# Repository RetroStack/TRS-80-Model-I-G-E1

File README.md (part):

# TRS-80 Model 1 (Rev G) Replica - E1

This project is a faithful reimplementation of the mainboard of the iconic TRS-80 Model 1 (Revision G) computer. My own revision, the E1, is designed to replicate the original system's functionality by using a PCB design 1-to-1 to the original, including components, interfaces, and even traces. The entire project is available under the MIT license.

## Project Details

### Latest Files

In the "Latest" folder, you'll find the most up-to-date design files, including:

- Gerber files suitable for popular online PCB manufacturers like [PCBWay](/Latest/TRS80_Model_I_G_E1_Gerber_PCBWay.zip) and [JLCPCB](/Latest/TRS80_Model_I_G_E1_Gerber_JLCPCB.zip). Most manufacturers should be fine with either.
- A Bill of Materials (BOM) in both [CSV](/Latest/TRS80_Model_I_G_E1_BOM.csv) and [PDF](/Latest/TRS80_Model_I_G_E1_BOM.pdf) formats. (Also, see the list below.)
- Layers exported in PDF and SVG formats.
- The [full schematics](/Latest/TRS80_Model_I_G_E1_Schematics.pdf) of the E1 replica which is 1:1 to the original G board.
- A simple [Assembly Guide](/Latest/TRS80_Model_I_G_E1_AssemblyGuide.pdf) in PDF format.

### Implementation

E1 has been implemented using KiCAD 7. The KiCAD project files are included in this repository.

### Assembly Instructions

For each step, check if there is a connection between pad 1, 8, 9, 16 on Z18 (all four corners of the dynamic RAM IC). That IC needs all 3 voltages with ground. If any of them are shorted, then you know what you did most recently. Finding the cause of the short should then be relatively easy.

1. (optional) Install sockets for all ICs. You probably want to skip Z3 and Z71, if you want to use DIP switches instead.
2. Install all diodes. These diodes are hard to read and if you accidentally mix them up, you might end up with incorrect voltages on the rails. Also, make sure to orient them correctly. There should be a black band on one side of the glass diode. Match this with the "thicker" side of the diode on the PCB. Installing first the shorter components will make sure you still can flip the board around and solder things easily.
3. Install all resistors. Resistors do not have an orientation. Skip the potentiometers for now. When installing the C*R67 (yes, there is a "C*"), this is an unmarked resistor between relay and the R21 potentiometer. This should be a 220 ohm 0.5W resistor (a bit larger than the others). There is another R67 which is next to Z42, which is a 4.7k Ohm resistor 0.25W (same size as most of the others).
4. Install all disc-like capacitors. Do not install the electrolytic capacitors yet! All other capacitors are rather small and orientation isn't important. The C58 next to the relay stays empty. Do not install it there. Instead, there is another (!!!) C58 next to the ROMs in the middle of the PCB.
5. Install all transistors, including the ones with the heatsinks. The TIP29 should go into Q3 (metal side away from board towards the Q3 label) while the TIP32C should go into Q6 (lay flat with heatsink; bend legs wit needle-nose pliers to fit). Don't forget to add thermal paste between heatsink and transistors. Make sure to add the screws and nuts and that it fits tightly as the screws themself connect traces. Not having them properly installed will result in a non-functioning system. The smaller black transistors have one flat side. These should all face towards the bottom of the board towards all the ICs (the middle leg needs to be bend slightly out to fit).
6. Install the crystal (no orientation), relay (match orientation on PCB; three legs towards the bottom), full-bridge rectifier (CR8; match "+" marking on component with PCB marking), all DIN connectors, both switches, keyboard connector (if bend, bend it upwards - towards the CPU to fit in the case), and potentiometers (only goes in one way). You can also install the DIP switches, if you go with that (numbers on the left side and "ON" label on the right).
7. Install all electrolytic capacitors. Make sure the orientation is correct! Modern capacitors mark the "-" side. On the PCB, the positive side is marked. All electrolytic capacitors on the PCB are oriented the same way EXCEPT C42 (!!!). Incorrect orientation may result in a small explosion (loud and smokey, but probably not dangerous).
8. Only install Z1 & Z2 to calibrate the power supply. Don't install any of the other ICs yet!!!
9. Get Multimeter ready in voltage mode. Connect power, turn on S1. If something starts to smell burned, turn S1 off and disconnect power.
10. Check voltage between pad 1 (-5V) and pad 16 (GND) on Z18. It should be around -5.1V to -5.2V. Since this is clamped with a zener diode, this should be pretty accurate. There is nothing that needs to be calibrated here. If the voltage goes beyond -5.3V, check R19 (may be really hot! careful!). If R19 is hot to the touch, your power supply is probably broken. (I've seen this on one power supply while another one didn't have that problem.)
11. Check voltage between pad 8 (+12V) and pad 16 (GND) on Z18. It should be around +12.0V. If it isn't, change the R10 potentiometer. If it is +/-0.5V off, then this is fine. But, try to get it as close to the desired voltage as possible.
12. (You need to calibrate +12V first before going to this next step!!!) Check voltage between pad 9 (+5V) and pad 16 (GND) on Z18. It should be around +5.0V. If it isn't, change the R5 potentiometer. If it is +/-0.5V off, then this is fine. But, also here, try to get it close to the desired voltage.
13. Re-check all the voltages after calibration, just to be sure.
14. Turn off S1 and disconnect power. Do this for each of the following steps. After each change, re-check the voltages at Z18 to find shorts quickly.
15. Start inserting the ICs. Focus on the 74LSxx ICs first. They are cheap and are easily recoverable in case there is a short somewhere and you start frying ICs. May be do 2-4 chips at a time and re-check the voltages at Z18. Do this systematically from left to right and top to bottom, so you know which you inserted most recently. If one of the voltages changes significantly at Z18 (+/- 2V and more), then you probably have a short with the most recent ICs. Do not insert the CPU, ROMs, character generator, and RAMs (static (2102) and dynamic ones (4116)) for now. They are expensive to replace if they fry.
16. Insert the 74Cxx ICs. These ICs are also cheap, but they are very sensitive. If all voltages are good, then they are good to install.
17. Connect to a monitor. Use a CRT, if possible, as video calibration is easier. LCD works too, but the reaction time is slow and requires a longer wait time after each change.
18. After turning on monitor and S1, you should see white blocks on a black background. If you don't see it, try changing R20 (vertical sync) and R21 (horizontal sync). If all fails, try to center both potentiometer. This usually results in a non-optimal picture, but a picture non-the-less. You can then calibrate.
19. (Don't forget to turn off system!) Insert the static video RAM (2102). These ICs only require +5V.
20. Now you need to configure the memory addresses and the memory configuration. With DIP switches, configure as follows:

- (memory location configuration) Z3: Switch 1 to the left, while all others are to the right. This is the configuration for 12k ROM and 16k RAM.
- (memory type configuration) Z71: Switch 1, 3, 5 to the right while all others are to the left. This is the configuration for 16k RAM modules.

21. Insert the dynamic RAM (4116). These ICs require all three voltages.
22. Insert CPU. Not much should have changed from the video calibration up until now. The next step will change that.
23. Insert character generator. Instead of white blocks, you should see (random) characters. The system doesn't clear the video memory yet since no ROM is installed.
24. Install ROM. This should be a Level II v1.3. If you don't have this, you probably need additional circuity to make these work. You can also burn the [diag ROM](https://github.com/misterblack1/trs80-diagnosticrom/blob/main/trs80m13diag.bin) on a 2k ROM to test the system. The diag ROM should work for all revisions of the TRS-80 Model 1.
25. At this point, you should see a prompt showing "Memory Size?" that keeps blinking (if it is the normal system ROM). The reason for the blinking is that the keyboard is not yet connected and the system recognizes keypresses. Install the keyboard with the IDC cable (if you installed a header).
26. Now, you should be able to use the system. Try to hold the left SHIFT key and press the right arrow key and the text size should increase, switching the video modes. (It is OK when some characters are skipped. That is normal.) The CLEAR key should reset it to the original video mode and clear the screen.
27. Try running a "Hello World!" program: 10 PRINT "Hello World!" (Return) 20 GOTO 10 (Return) RUN (Return). You can stop with the BREAK key.

### Ordering Instructions

When ordering the board from a PCB manufacturer, you can select the following to get a more faithful version of the board:

```
Dimension: 407mm x 184mm
Layers: 2
Base Material: FR-4 TG 135-140 (and up)
PCB Thickness: 1.6mm
PCB Color: Green
Silkscreen Color: White
Via Covering: Untented
Surface Finish: Lead Free HASL
Outer Copper Weight: 1oz
Gold Fingers / Card Edge: yes (chamfer: 30 degrees)
Castellated Holes: no
```

Additionally, supply the following comment for the manufacturer:

> Card edge is only on the upper right. The bottom right is just a connector and does not need to be chamfered.
>
> There are some missing pads on the top layer. That is correct. Please leave them as-is.

This addresses recurring questions from some of the interesting designs that were used on the original board which was replicated. See the ["Curiosities"](/Curiosities.md) page.

### Bill of Materials (BOM)

Below is a list of materials needed to assemble a complete system. Please note that the links and prices (scroll to the right to see them; as of January 22, 2024) will not be updated in the future and should only be used as a reference for locating the correct items.

Note: Links and alternatives are provided to assist you in finding the necessary components. I cannot guarantee the complete accuracy or reliability of all these links and alternatives. Please check it for yourself!

| Reference                                                                                                                                                                | Qty | Description                                                          | Source Comment                                               | Source Cost USD | Source Total Cost USD | Source                                                                                                                                 |
| ------------------------------------------------------------------------------------------------------------------------------------------------------------------------ | --- | -------------------------------------------------------------------- | ------------------------------------------------------------ | --------------- | --------------------- | -------------------------------------------------------------------------------------------------------------------------------------- |
| C1                                                                                                                                                                       | 1   | 220uF 16V polarized capacitor                                        |                                                              | 1.48            | 1.48                  | [Mouser](https://www.mouser.com/ProductDetail/598-227TTA050M)                                                                          |
| C2, C4, C5, C10, C11, C57                                                                                                                                                | 6   | 10uF 16V polarized capacitor                                         |                                                              | 0.29            | 1.74                  | [Mouser](https://www.mouser.com/ProductDetail/598-106RMR050M)                                                                          |
| C3, C7, C14, C15                                                                                                                                                         | 4   | 0.01uF 24V (103) capacitor                                           |                                                              | 0.23            | 0.92                  | [Mouser](https://www.mouser.com/ProductDetail/594-D103Z25Z5VF63L6R)                                                                    |
| C6                                                                                                                                                                       | 1   | 100uF 16V polarized capacitor                                        |                                                              | 0.37            | 0.37                  | [Mouser](https://www.mouser.com/ProductDetail/647-UVZ1J101MPD)                                                                         |
| C8                                                                                                                                                                       | 1   | 2200uF 35V polarized capacitor                                       |                                                              | 5.31            | 5.31                  | [Mouser](https://www.mouser.com/ProductDetail/598-228TTA063M)                                                                          |
| C9                                                                                                                                                                       | 1   | 10000uF 16V polarized capacitor                                      |                                                              | 7.87            | 7.87                  | [Mouser](https://www.mouser.com/ProductDetail/598-109TTA025M)                                                                          |
| C12, C13                                                                                                                                                                 | 2   | 470pF (471) capacitor                                                |                                                              | 0.23            | 0.46                  | [Mouser](https://www.mouser.com/ProductDetail/594-D471K20Y5PH6UJ5R)                                                                    |
| C16, C17, C18, C19, C22, C23, C28, C29, C30, C31, C32, C33, C34, C35, C36, C37, C38, C39, C40, C41, C44, C45, C46, C47, C48, C49, C50, C51, C52, C53, C54, C55, C56, C58 | 34  | 0.1uF 25V (104) capacitor                                            |                                                              | 0.17            | 5.78                  | [Mouser](https://www.mouser.com/ProductDetail/594-K104K10X7RF53L2)                                                                     |
| C20                                                                                                                                                                      | 1   | 330pF (331) capacitor                                                |                                                              | 0.3             | 0.3                   | [Mouser](https://www.mouser.com/ProductDetail/594-F331K29Y5RP6UK5R)                                                                    |
| C21                                                                                                                                                                      | 1   | 750pF (750) capacitor                                                |                                                              | 0.37            | 0.37                  | [Mouser](https://www.mouser.com/ProductDetail/80-C322C751K3G5TA)                                                                       |
| C24, C25                                                                                                                                                                 | 2   | 220pF (221) capacitor                                                |                                                              | 0.23            | 0.46                  | [Mouser](https://www.mouser.com/ProductDetail/594-D221K20Y5PF63J5R)                                                                    |
| C26                                                                                                                                                                      | 1   | 0.047uF (47nF) capacitor                                             |                                                              | 1.9             | 1.9                   | [Mouser](https://www.mouser.com/ProductDetail/594-222236755473)                                                                        |
| C27                                                                                                                                                                      | 1   | 0.022uF (22nF) capacitor                                             |                                                              | 1.34            | 1.34                  | [Mouser](https://www.mouser.com/ProductDetail/594-2222-366-45223)                                                                      |
| C42                                                                                                                                                                      | 1   | 22uF 16V polarized capacitor                                         |                                                              | 0.1             | 0.1                   | [Mouser](https://www.mouser.com/ProductDetail/710-860010372002)                                                                        |
| C43                                                                                                                                                                      | 1   | 47pF (47) capacitor                                                  |                                                              | 0.4             | 0.4                   | [Mouser](https://www.mouser.com/ProductDetail/594-S470K25SL0N63L6R)                                                                    |
| CR1                                                                                                                                                                      | 1   | 1N4735 Zener diode                                                   |                                                              | 0.25            | 0.25                  | [Mouser](https://www.mouser.com/ProductDetail/512-1N4735A)                                                                             |
| CR2                                                                                                                                                                      | 1   | 1N5231 Zener diode                                                   |                                                              | 0.15            | 0.15                  | [Mouser](https://www.mouser.com/ProductDetail/512-1N5231B)                                                                             |
| CR3, CR4, CR5, CR6, CR7                                                                                                                                                  | 5   | 1N4148                                                               | Diode                                                        | 0.1             | 0.5                   | [Mouser](https://www.mouser.com/ProductDetail/512-1N4148)                                                                              |
| CR8                                                                                                                                                                      | 1   | MDA202 Diode bridge, +ve/AC/AC/-ve                                   | Replacement                                                  | 0.61            | 0.61                  | [Mouser](https://www.mouser.com/ProductDetail/621-KBP210G)                                                                             |
| CR9, CR10                                                                                                                                                                | 2   | 1N982 Schottky diode                                                 | Replacement, Lower (39V instead of 75V)                      | 0.26            | 0.52                  | [Mouser](https://www.mouser.com/ProductDetail/78-1N4754A-TAP)                                                                          |
| J1, J2, J3                                                                                                                                                               | 3   | 5-pin DIN connector (5-pin DIN-5 stereo)                             | For metal connector only. The plastic plugs don't fit in it. | 0.386           | 1.158                 | [AliExpress](https://www.aliexpress.us/item/2255801077942335.html)                                                                     |
| J100                                                                                                                                                                     | 1   | 01x20 Generic connector, single row, 01x20                           |                                                              | 0.5             | 0.5                   | [Mouser](https://www.mouser.com/ProductDetail/649-1012937992002BLF)                                                                    |
| K1                                                                                                                                                                       | 1   | Relay SPST, Normally Open                                            | Slightly smaller than original                               | 14.84           | 14.84                 | [DigiKey](https://www.digikey.com/en/products/detail/sensata-cynergy3/S2-05P/4425813)                                                  |
| Q1                                                                                                                                                                       | 1   | 2N3904 0.2A Ic, 40V Vce, Small Signal NPN Transistor, TO-92          |                                                              | 0.35            | 0.35                  | [Mouser](https://www.mouser.com/ProductDetail/512-2N3904BU)                                                                            |
| Q2, Q5                                                                                                                                                                   | 2   | 2N3906 -0.2A Ic, -40V Vce, Small Signal PNP Transistor, TO-92        |                                                              | 0.28            | 0.56                  | [Mouser](https://www.mouser.com/ProductDetail/512-2N3906BU)                                                                            |
| Q3                                                                                                                                                                       | 1   | TIP29A (BCE) NPN transistor                                          |                                                              | 1.01            | 1.01                  | [Mouser](https://www.mouser.com/ProductDetail/863-TIP29AG)                                                                             |
| Q4                                                                                                                                                                       | 1   | 2N6594 (BEC) PNP transistor                                          | Replacement (Other: RS2040, MJ2955G)                         | 4.73            | 4.73                  | [Mouser](https://www.mouser.com/ProductDetail/863-MJ2955G)                                                                             |
| Q6                                                                                                                                                                       | 1   | MJE34 (BCE) PNP transistor                                           | Replacement                                                  | 0.67            | 0.67                  | [Mouser](https://www.mouser.com/ProductDetail/511-TIP32C)                                                                              |
| -                                                                                                                                                                        | 1   | Q4 Heatsink                                                          |                                                              | 1.01            | 1.01                  | [Mouser](https://www.mouser.com/ProductDetail/532-506007B00)                                                                           |
| -                                                                                                                                                                        | 1   | Q6 Heatsink                                                          | Smaller than original                                        | 0.3             | 0.3                   | [Mouser](https://www.mouser.com/ProductDetail/532-507302B00)                                                                           |
| R1                                                                                                                                                                       | 1   | 68 Resistor 0.25W                                                    |                                                              | 0.1             | 0.1                   | [Mouser](https://www.mouser.com/ProductDetail/603-CFR-25JB-52-68R)                                                                     |
| R2                                                                                                                                                                       | 1   | 2.7k Resistor 0.25W                                                  |                                                              | 0.1             | 0.1                   | [Mouser](https://www.mouser.com/ProductDetail/603-CFR-25JR-522K7)                                                                      |
| R3                                                                                                                                                                       | 1   | 750 Resistor 0.25W                                                   |                                                              | 0.1             | 0.1                   | [Mouser](https://www.mouser.com/ProductDetail/603-CFR-25JB-52-750R)                                                                    |
| R4                                                                                                                                                                       | 1   | 0.33 Resistor 2W                                                     |                                                              | 0.45            | 0.45                  | [Mouser](https://www.mouser.com/ProductDetail/603-CFR2WSJT-73-0R33)                                                                    |
| R5, R10                                                                                                                                                                  | 2   | 1k Potentiometer                                                     |                                                              | 0.57            | 1.14                  | [Mouser](https://www.mouser.com/ProductDetail/531-PT10H-1K-S)                                                                          |
| R6, R7, R16, R53                                                                                                                                                         | 4   | 1.2k Resistor 0.25W                                                  |                                                              | 0.1             | 0.4                   | [Mouser](https://www.mouser.com/ProductDetail/603-CFR-25JB-52-1K2)                                                                     |
| R8                                                                                                                                                                       | 1   | 100k Resistor 0.25W                                                  |                                                              | 0.1             | 0.1                   | [Mouser](https://www.mouser.com/ProductDetail/603-CFR-25JB-52-100K)                                                                    |
| R9, R11, R12                                                                                                                                                             | 3   | 3.3k Resistor 0.25W                                                  |                                                              | 0.1             | 0.3                   | [Mouser](https://www.mouser.com/ProductDetail/603-CFR-25JB-52-3K3)                                                                     |
| R13                                                                                                                                                                      | 1   | 2.2k Resistor 0.25W                                                  |                                                              | 0.1             | 0.1                   | [Mouser](https://www.mouser.com/ProductDetail/603-CFR-25JT-52-2K2)                                                                     |
| R14                                                                                                                                                                      | 1   | 12k Resistor 0.25W                                                   |                                                              | 0.1             | 0.1                   | [Mouser](https://www.mouser.com/ProductDetail/603-CFR-25JB-52-12K)                                                                     |
| R15                                                                                                                                                                      | 1   | 1.5k Resistor 0.25W                                                  |                                                              | 0.1             | 0.1                   | [Mouser](https://www.mouser.com/ProductDetail/603-CFR-25JT-52-1K5)                                                                     |
| R17                                                                                                                                                                      | 1   | 2k Resistor 0.25W                                                    |                                                              | 0.1             | 0.1                   | [Mouser](https://www.mouser.com/ProductDetail/603-CFR-25JB-52-2K)                                                                      |
| R18                                                                                                                                                                      | 1   | 5.6 Resistor 3W                                                      |                                                              | 0.57            | 0.57                  | [Mouser](https://www.mouser.com/ProductDetail/279-EP3WSS5R6J)                                                                          |
| R19, C_R67                                                                                                                                                               | 2   | 220 Resistor 0.5W                                                    |                                                              | 0.1             | 0.1                   | [Mouser](https://www.mouser.com/ProductDetail/603-CFR-50JB-52-220R)                                                                    |
| R20, R21                                                                                                                                                                 | 2   | 100k Potentiometer                                                   |                                                              | 0.57            | 1.14                  | [Mouser](https://www.mouser.com/ProductDetail/531-PT10H-100K-S)                                                                        |
| R22                                                                                                                                                                      | 1   | 75 Resistor 0.25W                                                    |                                                              | 0.1             | 0.1                   | [Mouser](https://www.mouser.com/ProductDetail/603-CFR-25JB-52-75R)                                                                     |
| R23                                                                                                                                                                      | 1   | 120 Resistor 0.25W                                                   |                                                              | 0.1             | 0.1                   | [Mouser](https://www.mouser.com/ProductDetail/603-CFR-25JB-52-120R)                                                                    |
| R24                                                                                                                                                                      | 1   | 680k Resistor 0.25W                                                  |                                                              | 0.1             | 0.1                   | [Mouser](https://www.mouser.com/ProductDetail/603-CFR-25JB-52-680K)                                                                    |
| R25                                                                                                                                                                      | 1   | 1.6M Resistor 0.25W                                                  |                                                              | 0.1             | 0.1                   | [Mouser](https://www.mouser.com/ProductDetail/603-CFR-25JB-52-1M6)                                                                     |
| R26, R42                                                                                                                                                                 | 2   | 1M Resistor 0.25W                                                    |                                                              | 0.1             | 0.2                   | [Mouser](https://www.mouser.com/ProductDetail/603-CFR-25JT-52-1M)                                                                      |
| R27, R64                                                                                                                                                                 | 2   | 330 Resistor 0.25W                                                   |                                                              | 0.1             | 0.2                   | [Mouser](https://www.mouser.com/ProductDetail/603-CFR-25JB-52-330R)                                                                    |
| R28                                                                                                                                                                      | 1   | 270 Resistor 0.25W                                                   |                                                              | 0.1             | 0.1                   | [Mouser](https://www.mouser.com/ProductDetail/603-CFR-25JB-52-270R)                                                                    |
| R29                                                                                                                                                                      | 1   | 1.8k Resistor 0.25W                                                  |                                                              | 0.1             | 0.1                   | [Mouser](https://www.mouser.com/ProductDetail/603-CFR-25JB-52-1K8)                                                                     |
| R30                                                                                                                                                                      | 1   | 47 Resistor 0.25W                                                    |                                                              | 0.1             | 0.1                   | [Mouser](https://www.mouser.com/ProductDetail/603-CFR-25JB-52-47R)                                                                     |
| R31                                                                                                                                                                      | 1   | 10 Resistor 0.25W                                                    |                                                              | 0.1             | 0.1                   | [Mouser](https://www.mouser.com/ProductDetail/603-CFR-25JT-52-10R)                                                                     |
| R32, R43, R44, R47, R65                                                                                                                                                  | 5   | 10k Resistor 0.25W                                                   |                                                              | 0.1             | 0.5                   | [Mouser](https://www.mouser.com/ProductDetail/603-CFR-25JB-52-10K)                                                                     |
| R33, R36                                                                                                                                                                 | 2   | 360k Resistor 0.25W                                                  |                                                              | 0.1             | 0.2                   | [Mouser](https://www.mouser.com/ProductDetail/603-CFR-25JB-52-360K)                                                                    |
| R34, R35, R38, R41, R45                                                                                                                                                  | 5   | 470k Resistor 0.25W                                                  |                                                              | 0.1             | 0.5                   | [Mouser](https://www.mouser.com/ProductDetail/603-CFR-25JB-52-470K)                                                                    |
| R37                                                                                                                                                                      | 1   | 560k Resistor 0.25W                                                  |                                                              | 0.1             | 0.1                   | [Mouser](https://www.mouser.com/ProductDetail/603-CFR-25JB-52-560K)                                                                    |
| R39, R40, R48, R49, R50, R51, R57, R58, R59, R60, R61, R62, R63, R66, R67, R68, R69                                                                                      | 17  | 4.7k Resistor 0.25W                                                  |                                                              | 0.1             | 1.7                   | [Mouser](https://www.mouser.com/ProductDetail/603-CFR-25JB-52-4K7)                                                                     |
| R46, R52                                                                                                                                                                 | 2   | 910 Resistor 0.25W                                                   |                                                              | 0.1             | 0.2                   | [Mouser](https://www.mouser.com/ProductDetail/603-CFR-25JB-52-910R)                                                                    |
| R54, R55                                                                                                                                                                 | 2   | 7.5k Resistor 0.25W                                                  |                                                              | 0.1             | 0.2                   | [Mouser](https://www.mouser.com/ProductDetail/603-CFR-25JB-52-7K5)                                                                     |
| R56                                                                                                                                                                      | 1   | 220k Resistor 0.25W                                                  |                                                              | 0.1             | 0.1                   | [Mouser](https://www.mouser.com/ProductDetail/603-CFR-25JB-52-220K)                                                                    |
| S1                                                                                                                                                                       | 1   | Power 4PST                                                           | No Cap                                                       | 4.34            | 4.34                  | [DigiKey](https://www.digikey.com/en/products/detail/c-k/F4UEE/417520)                                                                 |
| S2                                                                                                                                                                       | 1   | Reset DPST                                                           | Red Cap                                                      | 1.815           | 1.815                 | [AliExpress](https://www.aliexpress.us/item/3256804467086494.html)                                                                     |
| Y1                                                                                                                                                                       | 1   | 10.6445 MHz Two pin crystal                                          | Only 10.6MHz                                                 | 0.73            | 0.73                  | [Mouser](https://www.mouser.com/ProductDetail/449-LFXTAL028537BULK)                                                                    |
| Z1, Z2                                                                                                                                                                   | 2   | LM723C Linear Regulator (adjustable)                                 |                                                              | 1.04            | 2.08                  | [Mouser](https://www.mouser.com/ProductDetail/595-UA723CN)                                                                             |
| Z3, Z71                                                                                                                                                                  | 2   | 8-Bit DIP Switch                                                     | Replacement                                                  | 2.07            | 4.14                  | [Mouser](https://www.mouser.com/ProductDetail/710-418117270908)                                                                        |
| Z4                                                                                                                                                                       | 1   | LM3900 Quad operational amplifier                                    |                                                              | 0.6             | 0.6                   | [Mouser](https://www.mouser.com/ProductDetail/595-LM3900NE4)                                                                           |
| Z5                                                                                                                                                                       | 1   | 74C00 quad 2-input NAND gate                                         | 74HC00 works in a pinch, but suboptimal video.               | ~2.50           | ~2.50                 | eBay/Jameco                                                                                                                            |
| Z6, Z57                                                                                                                                                                  | 2   | 74C04 Hex Inverter                                                   | 74HC00 works in a pinch, but suboptimal video.               | 2.49            | 4.98                  | [Jameco](https://www.jameco.com/webapp/wcs/stores/servlet/ProductDisplay?storeId=10001&langId=-1&catalogId=10001&productId=44231)      |
| Z7, Z69, Z70                                                                                                                                                             | 3   | 74LS74 Dual D Flip-flop, Set & Reset                                 |                                                              | 0.49            | 1.47                  | [Mouser](https://www.mouser.com/ProductDetail/595-SN74LS74AN)                                                                          |
| Z8                                                                                                                                                                       | 1   | 74LS153 Dual Multiplexer 4 to 1                                      |                                                              | 1.13            | 1.13                  | [Mouser](https://www.mouser.com/ProductDetail/595-SN74LS153N)                                                                          |
| Z9, Z42, Z52                                                                                                                                                             | 3   | 74LS04 Hex Inverter                                                  |                                                              | 0.67            | 2.01                  | [Mouser](https://www.mouser.com/ProductDetail/595-SN74LS04N)                                                                           |
| Z10, Z11                                                                                                                                                                 | 2   | 74LS166 Shift Register 8-bit, parallel load                          |                                                              | 1.24            | 2.48                  | [Mouser](https://www.mouser.com/ProductDetail/595-SN74LS166AN)                                                                         |
| Z12, Z32, Z50, Z65                                                                                                                                                       | 4   | 74LS93 Divide by 2 & 8 counter                                       |                                                              | 3.04            | 12.16                 | [Mouser](https://www.mouser.com/ProductDetail/595-SN74LS93N)                                                                           |
| Z13, Z14, Z15, Z16, Z17, Z18, Z19, Z20                                                                                                                                   | 8   | 4116 16kBit x 1 Bit Dynamic RAM                                      |                                                              | 3.95            | 31.6                  | [Jameco](https://www.jameco.com/z/4116-15-Major-Brands-IC-4116-15-DRAM-16-384-Bit-16Kx1-150ns-5V_41339.html)                           |
| Z21                                                                                                                                                                      | 1   | 74LS156 Dual 2 to 4 lines Decoder/Demultiplexer, Open Collector      |                                                              | 0.75            | 0.75                  | [Mouser](https://www.mouser.com/ProductDetail/595-SN74LS156N)                                                                          |
| Z22, Z38, Z39, Z44, Z55, Z60, Z67, Z68, Z72, Z75, Z76                                                                                                                    | 11  | 74LS367 Hex buffer 3-State outputs                                   |                                                              | 1.44            | 15.84                 | [Mouser](https://www.mouser.com/ProductDetail/595-SN74LS367AN)                                                                         |
| Z23, Z25, Z36, Z73                                                                                                                                                       | 4   | 74LS32 Quad 2-input OR                                               |                                                              | 0.56            | 2.24                  | [Mouser](https://www.mouser.com/ProductDetail/595-SN74LS32N)                                                                           |
| Z24, Z53                                                                                                                                                                 | 2   | 74LS132 Quad 2-input NAND Schmitt trigger                            |                                                              | 1.03            | 2.06                  | [Mouser](https://www.mouser.com/ProductDetail/595-SN74LS132N)                                                                          |
| Z26                                                                                                                                                                      | 1   | 74LS20 Dual 4-input NAND                                             |                                                              | 1.28            | 1.28                  | [Mouser](https://www.mouser.com/ProductDetail/595-SN74LS20N)                                                                           |
| Z27, Z59                                                                                                                                                                 | 2   | 74LS175 4-bit D Flip-Flop, reset                                     |                                                              | 1.02            | 2.04                  | [Mouser](https://www.mouser.com/ProductDetail/595-SN74LS175N)                                                                          |
| Z28                                                                                                                                                                      | 1   | 74LS174 Hex D-type Flip-Flop, reset                                  |                                                              | 1.12            | 1.12                  | [Mouser](https://www.mouser.com/ProductDetail/595-SN74LS174N)                                                                          |
| Z29                                                                                                                                                                      | 1   | MCM6670 128 x 7 x 5 Character Generator                              | Adapter needed                                               |                 | 0                     | [GitHub](https://github.com/RetroStack/MCM776x_CharGen_Adapter)                                                                        |
| Z30, Z37                                                                                                                                                                 | 2   | 74LS02 quad 2-input NOR gate                                         |                                                              | 0.55            | 1.1                   | [Mouser](https://www.mouser.com/ProductDetail/595-SN74LS02N)                                                                           |
| Z31, Z35, Z43, Z49, Z51, Z64                                                                                                                                             | 6   | 74LS157 Quad 2 to 1 line Multiplexer                                 |                                                              | 0.88            | 5.28                  | [Mouser](https://www.mouser.com/ProductDetail/595-SN74LS157N)                                                                          |
| Z33                                                                                                                                                                      | 1   | 2364 (20-pin Low) 2364 64kBit (8kb x 8) PROM                         | Adapter needed                                               |                 | 0                     | -                                                                                                                                      |
| Z34                                                                                                                                                                      | 1   | 2332 (20- & 21-pin Low) 2332 32kBit (4kb x 8) PROM                   | Adapter needed                                               |                 | 0                     | -                                                                                                                                      |
| Z40                                                                                                                                                                      | 1   | Z80 CPU                                                              |                                                              | 9.62            | 9.62                  | [Mouser](https://www.mouser.com/ProductDetail/692-Z84C0010PEG)                                                                         |
| Z41                                                                                                                                                                      | 1   | 75452 Dual-Peripheral Drivers for High-Current, High-Speed Switching |                                                              | 0.9             | 0.9                   | [Mouser](https://www.mouser.com/ProductDetail/595-SN75452BP)                                                                           |
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
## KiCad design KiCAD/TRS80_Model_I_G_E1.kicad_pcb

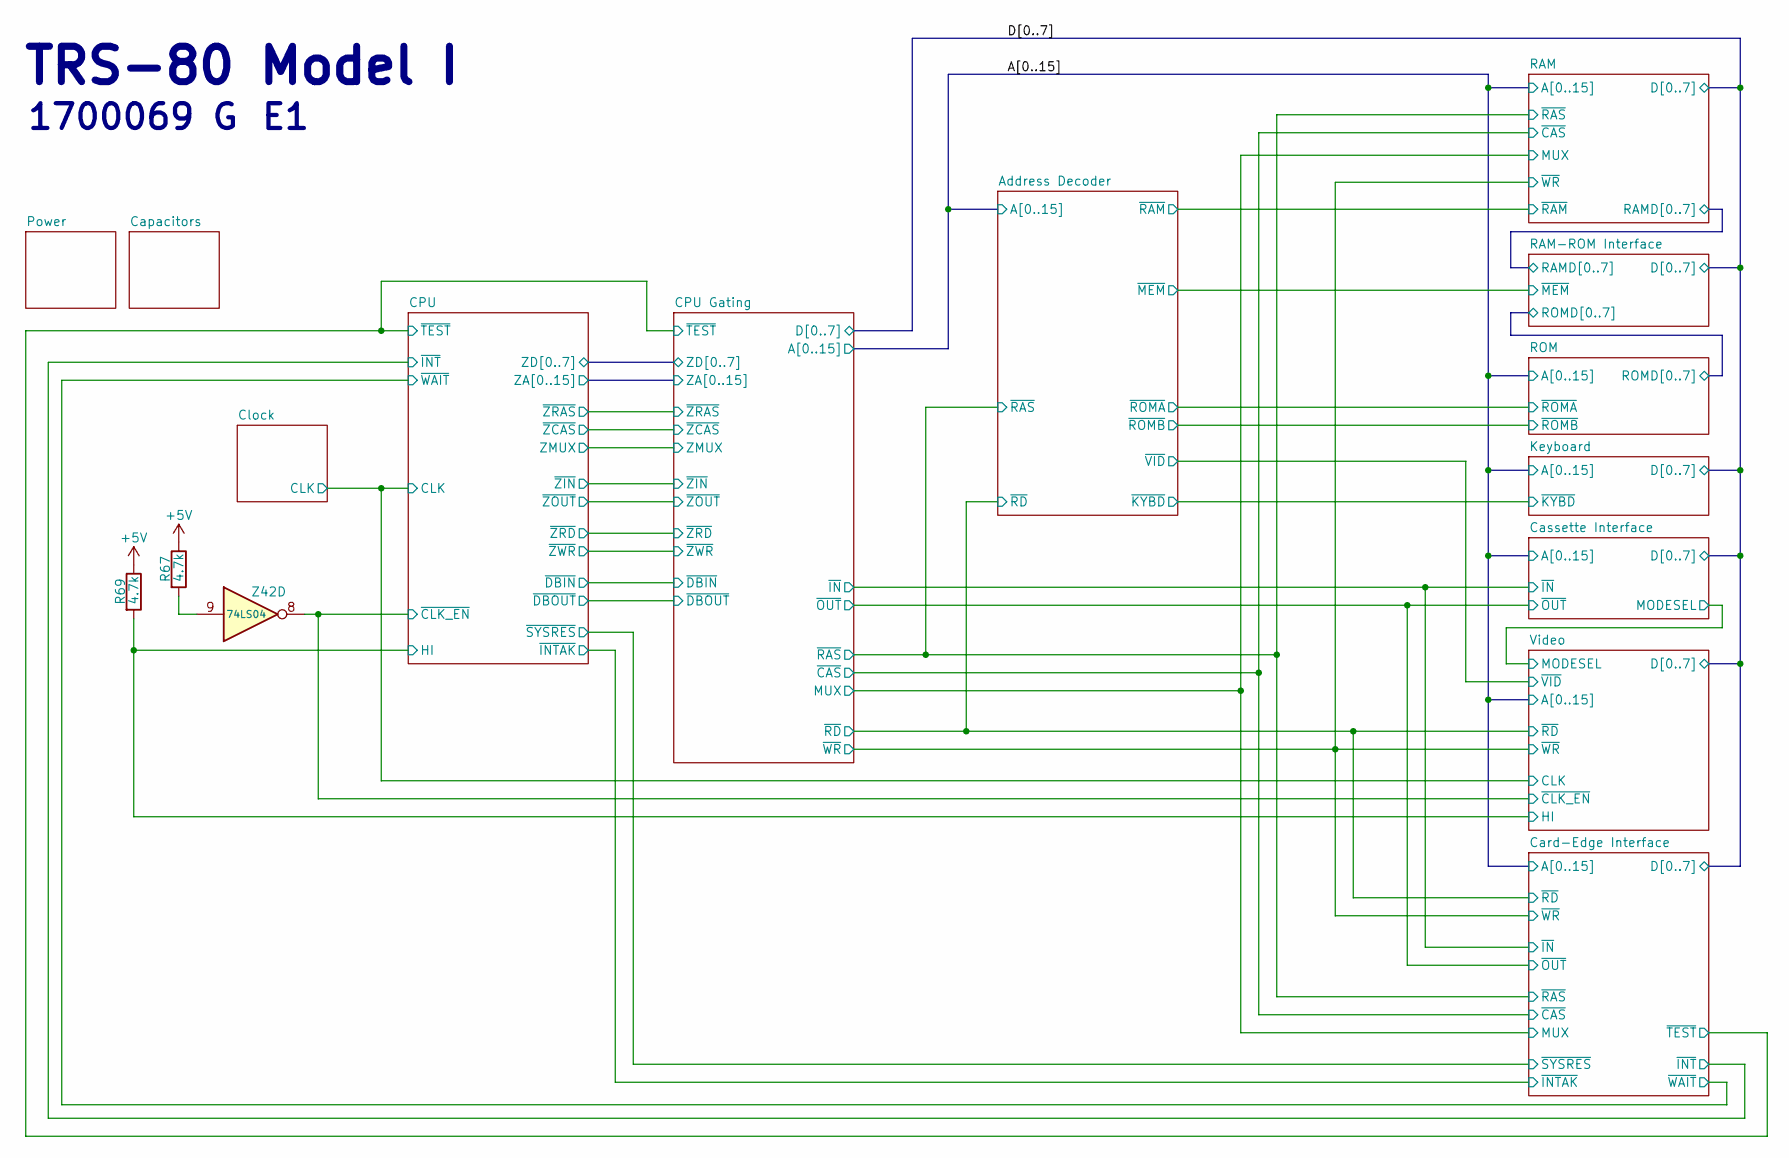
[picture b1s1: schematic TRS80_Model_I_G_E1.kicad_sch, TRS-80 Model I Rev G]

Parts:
R67, R69: 4.7k; TRS80_Model_I_R_0.25W
Z42: 74LS04; TRS80_Model_I_DIP14

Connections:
+5V: R67.1, R69.1; also elsewhere on the board
/CPU/HI: R69.2; also elsewhere on the board
/CPU/~CLK_EN: Z42.8; also elsewhere on the board
unnamed: R67.2, Z42.9

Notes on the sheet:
TRS-80 Model I
1700069 G

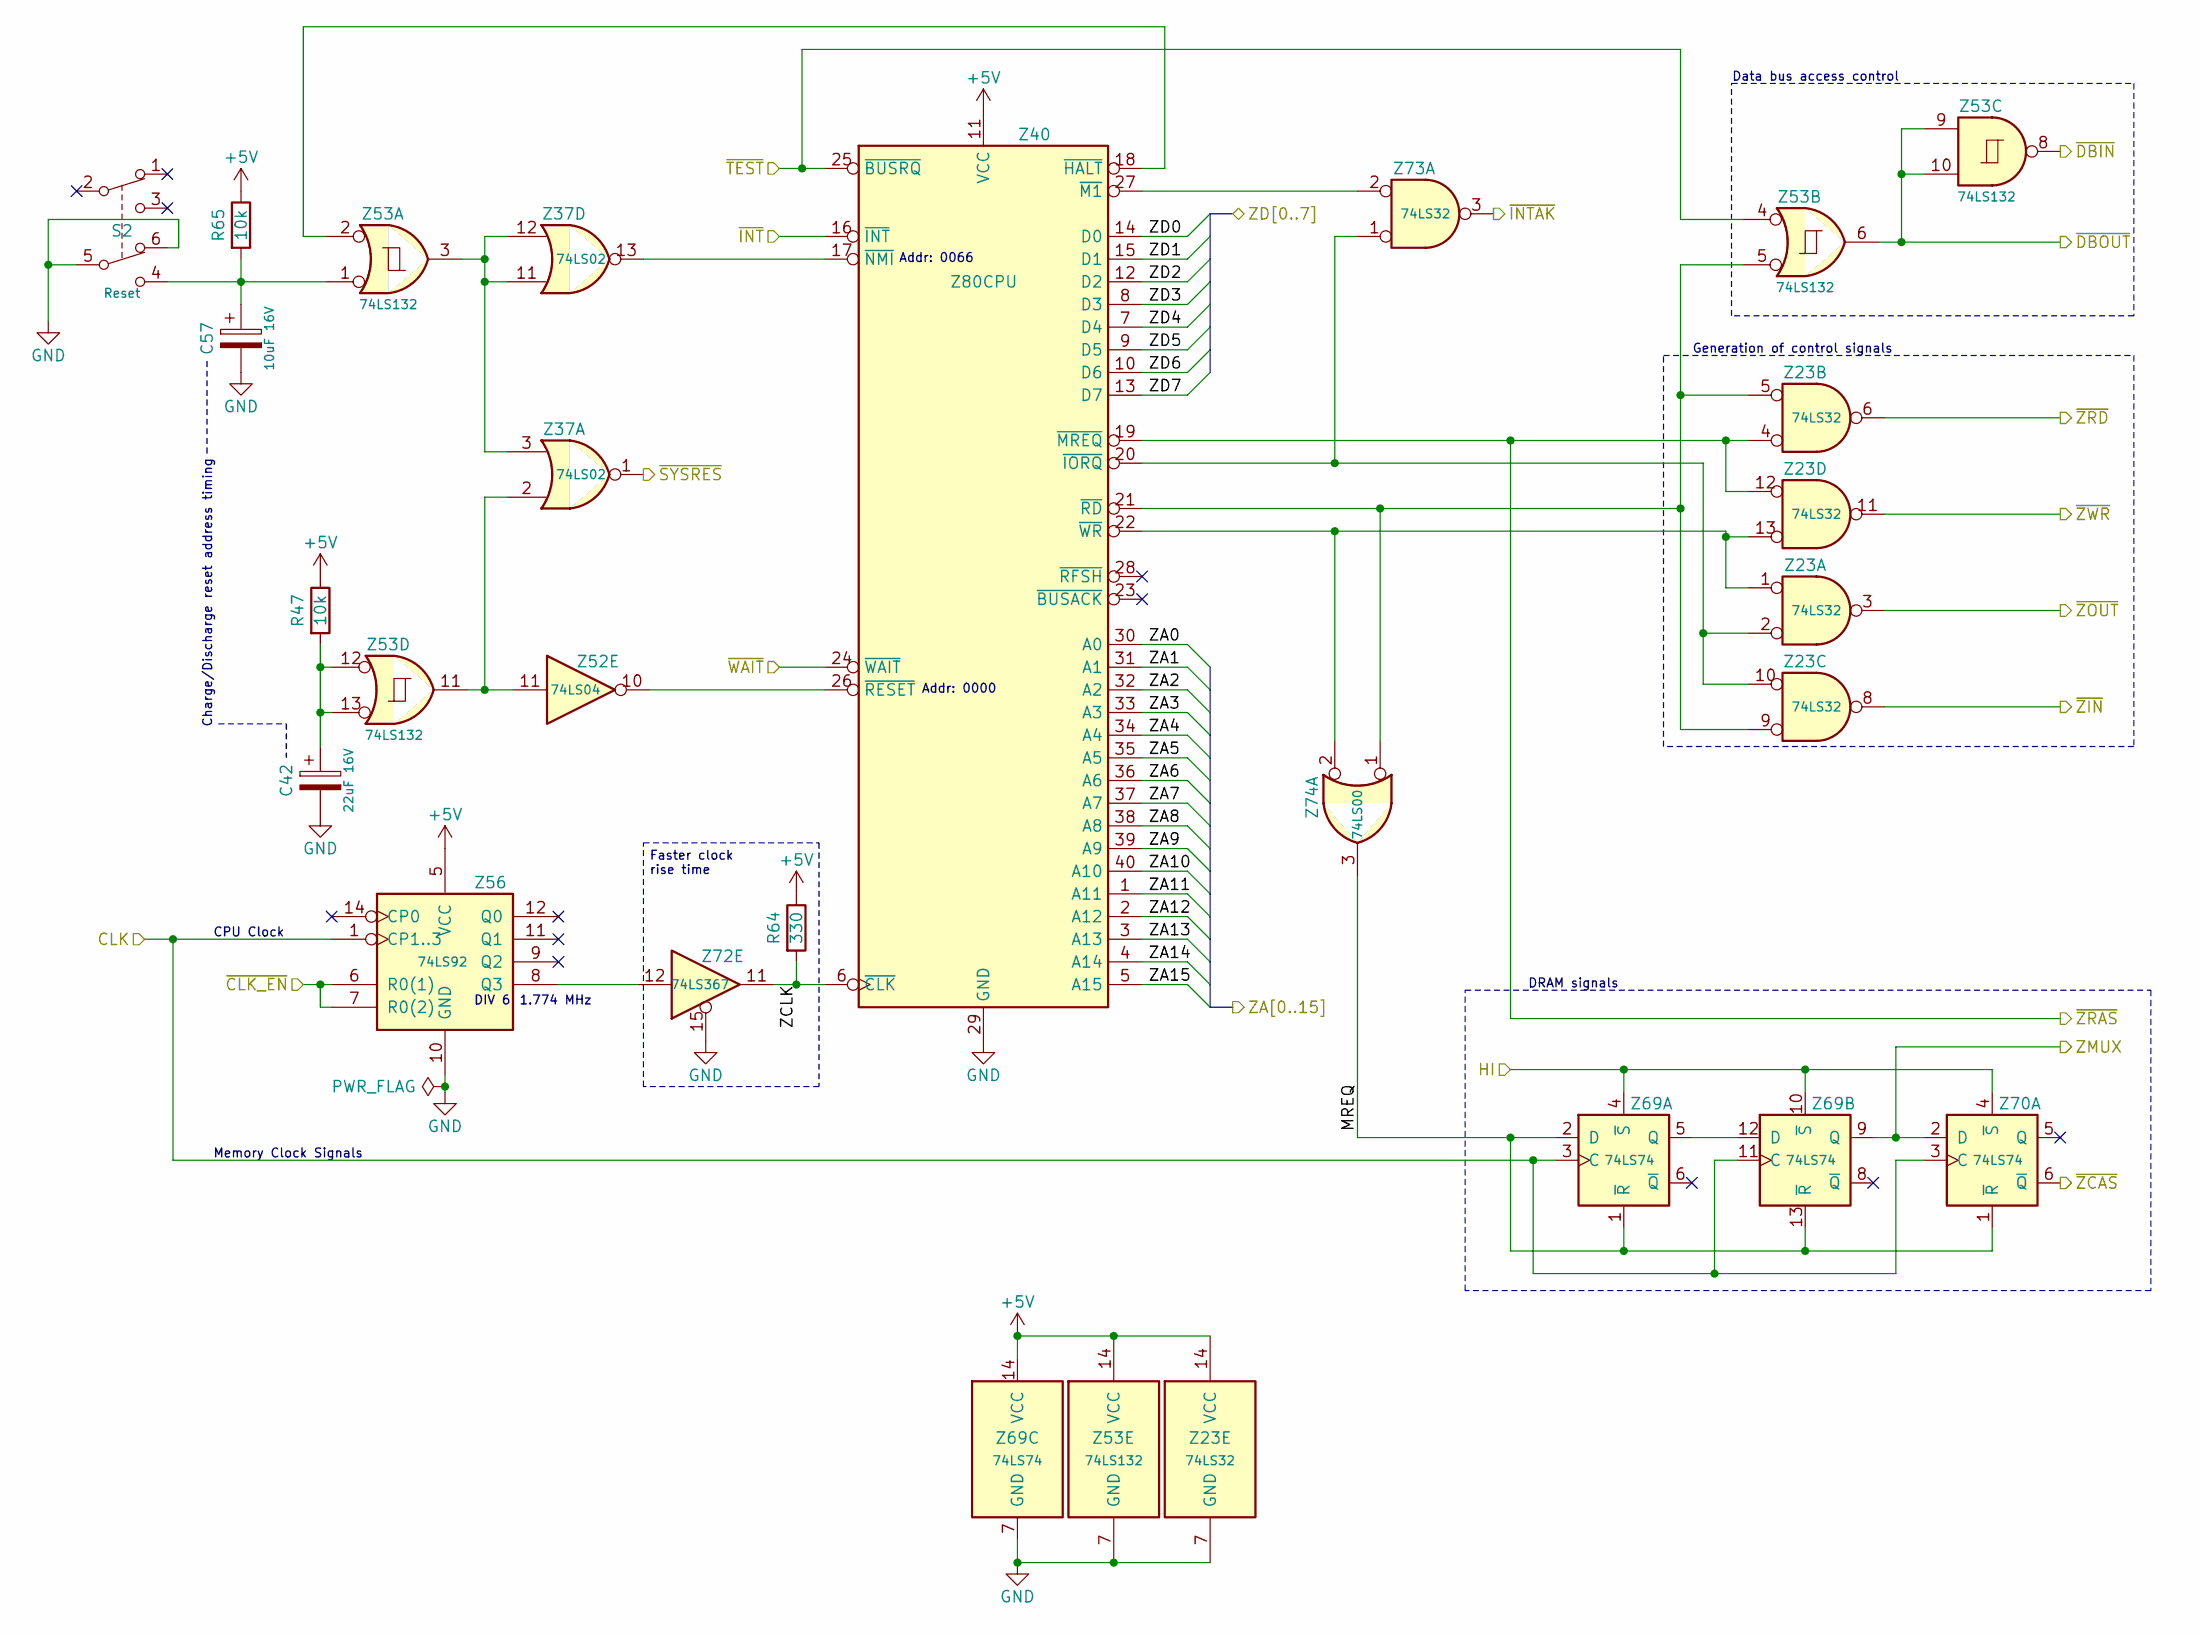
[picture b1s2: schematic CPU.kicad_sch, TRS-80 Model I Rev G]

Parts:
C42: 22uF 16V; TRS80_Model_I_C_Pol_Radial_6.3D_2.5P
C57: 10uF 16V; TRS80_Model_I_C_Pol_Radial_5D_2.5P
R47, R65: 10k; TRS80_Model_I_R_0.25W
R64: 330; TRS80_Model_I_R_0.25W
S2: Reset; TRS80_Model_I_Sw_Small
Z23, Z73: 74LS32; TRS80_Model_I_DIP14
Z37: 74LS02; TRS80_Model_I_DIP14
Z40: Z80CPU; TRS80_Model_I_DIP40
Z52: 74LS04; TRS80_Model_I_DIP14
Z53: 74LS132; TRS80_Model_I_DIP14
Z56: 74LS92; TRS80_Model_I_DIP14
Z69, Z70: 74LS74; TRS80_Model_I_DIP14
Z72: 74LS367; TRS80_Model_I_DIP16
Z74: 74LS00; TRS80_Model_I_DIP14

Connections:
+5V: R47.1, R64.1, R65.1, Z23.14 (VCC), Z40.11 (VCC), Z53.14 (VCC), Z56.5 (VCC), Z69.14 (VCC); also elsewhere on the board
/CPU Gating/ZA0: Z40.30 (A0); also elsewhere on the board
/CPU Gating/ZA1: Z40.31 (A1); also elsewhere on the board
/CPU Gating/ZA2: Z40.32 (A2); also elsewhere on the board
/CPU Gating/ZA3: Z40.33 (A3); also elsewhere on the board
/CPU Gating/ZA4: Z40.34 (A4); also elsewhere on the board
/CPU Gating/ZA5: Z40.35 (A5); also elsewhere on the board
/CPU Gating/ZA6: Z40.36 (A6); also elsewhere on the board
/CPU Gating/ZA7: Z40.37 (A7); also elsewhere on the board
/CPU Gating/ZA8: Z40.38 (A8); also elsewhere on the board
/CPU Gating/ZA9: Z40.39 (A9); also elsewhere on the board
/CPU Gating/ZA10: Z40.40 (A10); also elsewhere on the board
/CPU Gating/ZA11: Z40.1 (A11); also elsewhere on the board
/CPU Gating/ZA12: Z40.2 (A12); also elsewhere on the board
/CPU Gating/ZA13: Z40.3 (A13); also elsewhere on the board
/CPU Gating/ZA14: Z40.4 (A14); also elsewhere on the board
/CPU Gating/ZA15: Z40.5 (A15); also elsewhere on the board
/CPU Gating/ZD0: Z40.14 (D0); also elsewhere on the board
/CPU Gating/ZD1: Z40.15 (D1); also elsewhere on the board
/CPU Gating/ZD2: Z40.12 (D2); also elsewhere on the board
/CPU Gating/ZD3: Z40.8 (D3); also elsewhere on the board
/CPU Gating/ZD4: Z40.7 (D4); also elsewhere on the board
/CPU Gating/ZD5: Z40.9 (D5); also elsewhere on the board
/CPU Gating/ZD6: Z40.10 (D6); also elsewhere on the board
/CPU Gating/ZD7: Z40.13 (D7); also elsewhere on the board
/CPU Gating/ZMUX: Z69.9 (Q), Z70.2 (D); also elsewhere on the board
/CPU Gating/~DBIN: Z53.8; also elsewhere on the board
/CPU Gating/~DBOUT: Z53.6, Z53.9, Z53.10; also elsewhere on the board
/CPU Gating/~TEST: Z40.25 (~BUSRQ), Z53.4; also elsewhere on the board
/CPU Gating/~ZCAS: Z70.6 (~Q); also elsewhere on the board
/CPU Gating/~ZIN: Z23.8; also elsewhere on the board
/CPU Gating/~ZOUT: Z23.3; also elsewhere on the board
/CPU Gating/~ZRAS: Z23.4, Z23.12, Z40.19 (~MREQ); also elsewhere on the board
/CPU Gating/~ZRD: Z23.6; also elsewhere on the board
/CPU Gating/~ZWR: Z23.11; also elsewhere on the board
/CPU/CLK: Z56.1 (CP1..3), Z69.3 (C), Z69.11 (C), Z70.3 (C); also elsewhere on the board
/CPU/HI: Z69.4 (~S), Z69.10 (~S), Z70.4 (~S); also elsewhere on the board
/CPU/MREQ: Z69.1 (~R), Z69.2 (D), Z69.13 (~R), Z70.1 (~R), Z74.3
/CPU/ZCLK: R64.2, Z40.6 (~CLK), Z72.11
/CPU/~CLK_EN: Z56.6 (R0(1)), Z56.7 (R0(2)); also elsewhere on the board
/CPU/~INTAK: Z73.3; also elsewhere on the board
/CPU/~INT: Z40.16 (~INT); also elsewhere on the board
/CPU/~SYSRES: Z37.1; also elsewhere on the board
/CPU/~WAIT: Z40.24 (~WAIT); also elsewhere on the board
GND: C42.2, C57.2, S2.5, S2.6, Z23.7 (GND), Z40.29 (GND), Z53.7 (GND), Z56.10 (GND), Z69.7 (GND), Z72.15; also elsewhere on the board
unnamed: C42.1, R47.2, Z53.12, Z53.13
unnamed: C57.1, R65.2, S2.4, Z53.1
unnamed: Z37.2, Z52.11, Z53.11
unnamed: Z37.3, Z37.11, Z37.12, Z53.3
unnamed: Z40.18 (~HALT), Z53.2
unnamed: Z23.2, Z23.10, Z40.20 (~IORQ), Z73.1
unnamed: Z40.27 (~M1), Z73.2
unnamed: Z37.13, Z40.17 (~NMI)
unnamed: Z23.5, Z23.9, Z40.21 (~RD), Z53.5, Z74.1
unnamed: Z40.26 (~RESET), Z52.10
unnamed: Z23.1, Z23.13, Z40.22 (~WR), Z74.2
unnamed: Z56.8 (Q3), Z72.12
unnamed: Z69.5 (Q), Z69.12 (D)

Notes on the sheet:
Data bus access control
DIV 6
Generation of control signals
DRAM signals
1.774 MHz
Faster clock rise time
Memory Clock Signals
CPU Clock
Addr: 0000
Charge/Discharge reset address timing
Addr: 0066

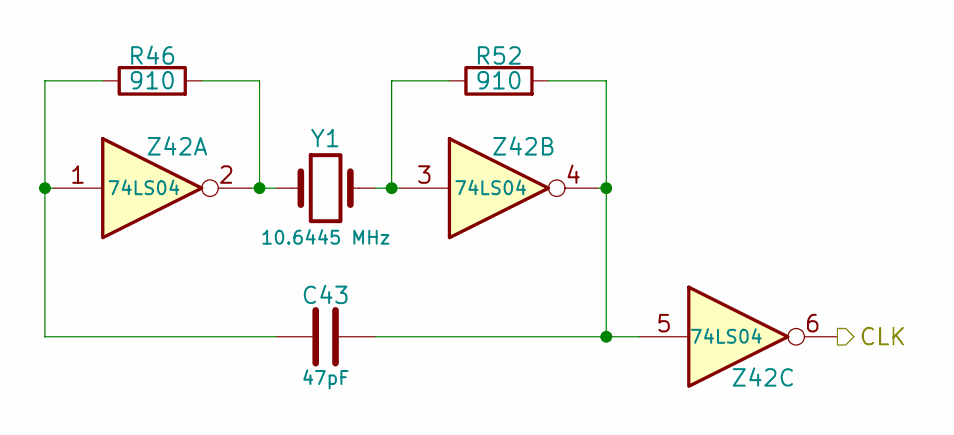
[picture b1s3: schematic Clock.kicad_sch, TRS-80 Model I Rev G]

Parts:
C43: 47pF; TRS80_Model_I_C_Disc_9.5L_4W_6P_Small
R46, R52: 910; TRS80_Model_I_R_0.25W
Y1: 10.6445 MHz; TRS80_Model_I_Crystal
Z42: 74LS04; TRS80_Model_I_DIP14

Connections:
/CPU/CLK: Z42.6; also elsewhere on the board
unnamed: C43.1, R46.1, Z42.1
unnamed: C43.2, R52.2, Z42.4, Z42.5
unnamed: R46.2, Y1.1, Z42.2
unnamed: R52.1, Y1.2, Z42.3

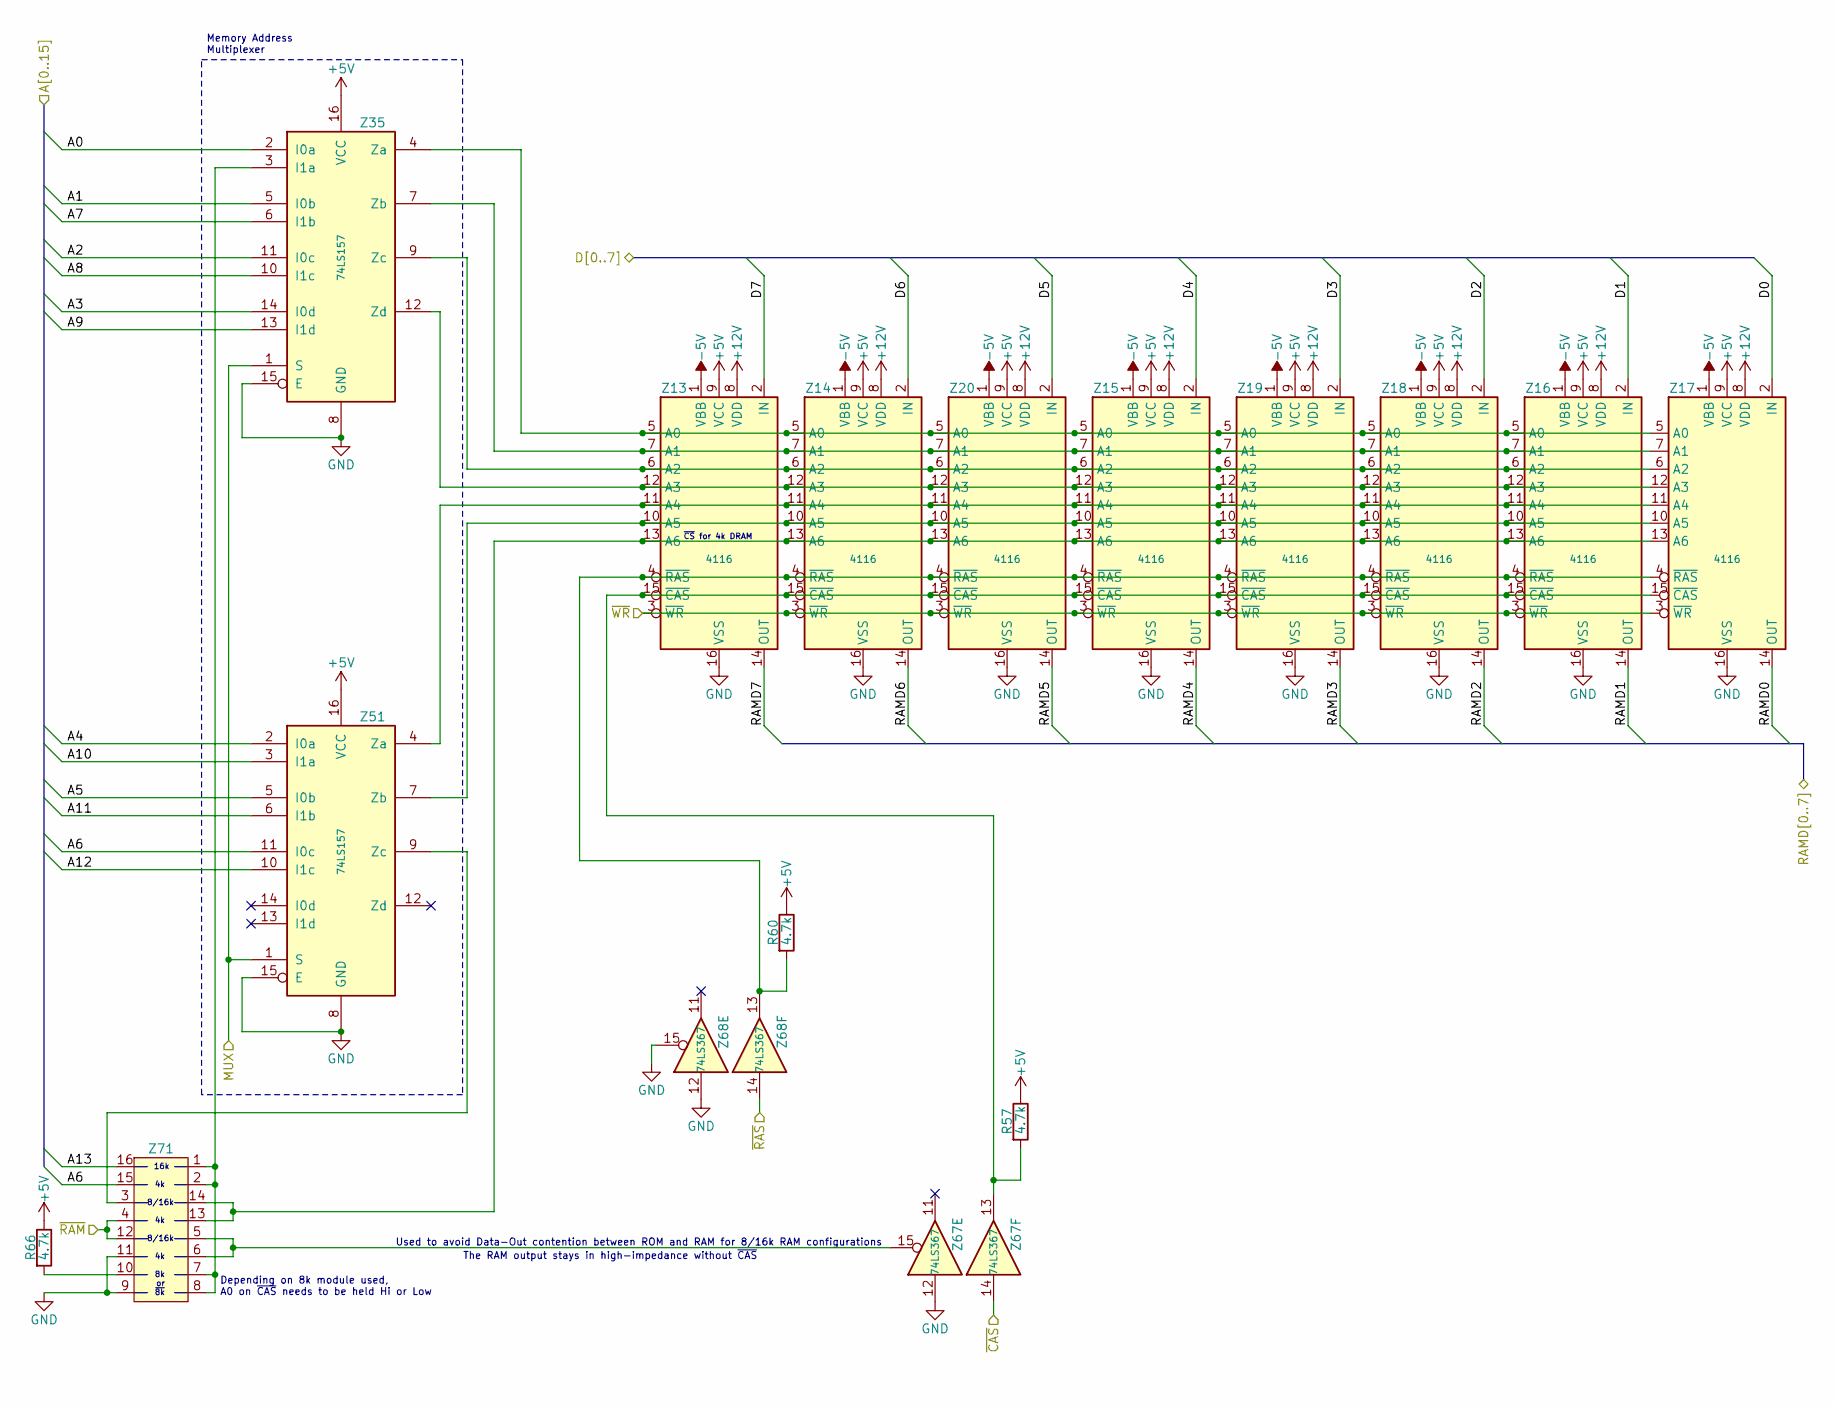
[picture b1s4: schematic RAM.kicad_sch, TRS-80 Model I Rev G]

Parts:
R57, R60, R66: 4.7k; TRS80_Model_I_R_0.25W
Z13, Z14, Z15, Z16, Z17, Z18, Z19, Z20: 4116; DIP-16_W7.62mm
Z35, Z51: 74LS157; TRS80_Model_I_DIP16
Z67, Z68: 74LS367; TRS80_Model_I_DIP16
Z71: DIP-16_W7.62mm

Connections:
+5V: R57.1, R60.1, R66.1, Z13.9 (VCC), Z14.9 (VCC), Z15.9 (VCC), Z16.9 (VCC), Z17.9 (VCC), Z18.9 (VCC), Z19.9 (VCC), Z20.9 (VCC), Z35.16 (VCC), Z51.16 (VCC); also elsewhere on the board
+12V: Z13.8 (VDD), Z14.8 (VDD), Z15.8 (VDD), Z16.8 (VDD), Z17.8 (VDD), Z18.8 (VDD), Z19.8 (VDD), Z20.8 (VDD); also elsewhere on the board
-5V: Z13.1 (VBB), Z14.1 (VBB), Z15.1 (VBB), Z16.1 (VBB), Z17.1 (VBB), Z18.1 (VBB), Z19.1 (VBB), Z20.1 (VBB); also elsewhere on the board
/A0: Z35.2 (I0a); also elsewhere on the board
/A1: Z35.5 (I0b); also elsewhere on the board
/A2: Z35.11 (I0c); also elsewhere on the board
/A3: Z35.14 (I0d); also elsewhere on the board
/A4: Z51.2 (I0a); also elsewhere on the board
/A5: Z51.5 (I0b); also elsewhere on the board
/A6: Z51.11 (I0c), Z71.15; also elsewhere on the board
/A7: Z35.6 (I1b); also elsewhere on the board
/A8: Z35.10 (I1c); also elsewhere on the board
/A9: Z35.13 (I1d); also elsewhere on the board
/A10: Z51.3 (I1a); also elsewhere on the board
/A11: Z51.6 (I1b); also elsewhere on the board
/A12: Z51.10 (I1c); also elsewhere on the board
/A13: Z71.16; also elsewhere on the board
/Address Decoder/~RAM: Z71.4, Z71.12; also elsewhere on the board
/Address Decoder/~RAS: Z68.14; also elsewhere on the board
/CPU Gating/MUX: Z35.1 (S), Z51.1 (S); also elsewhere on the board
/CPU Gating/~CAS: Z67.14; also elsewhere on the board
/CPU Gating/~WR: Z13.3 (~WR), Z14.3 (~WR), Z15.3 (~WR), Z16.3 (~WR), Z17.3 (~WR), Z18.3 (~WR), Z19.3 (~WR), Z20.3 (~WR); also elsewhere on the board
/D0: Z17.2 (IN); also elsewhere on the board
/D1: Z16.2 (IN); also elsewhere on the board
/D2: Z18.2 (IN); also elsewhere on the board
/D3: Z19.2 (IN); also elsewhere on the board
/D4: Z15.2 (IN); also elsewhere on the board
/D5: Z20.2 (IN); also elsewhere on the board
/D6: Z14.2 (IN); also elsewhere on the board
/D7: Z13.2 (IN); also elsewhere on the board
/RAM-ROM Interface/ROMD0: Z17.14 (OUT); also elsewhere on the board
/RAM-ROM Interface/ROMD1: Z16.14 (OUT); also elsewhere on the board
/RAM-ROM Interface/ROMD2: Z18.14 (OUT); also elsewhere on the board
/RAM-ROM Interface/ROMD3: Z19.14 (OUT); also elsewhere on the board
/RAM-ROM Interface/ROMD4: Z15.14 (OUT); also elsewhere on the board
/RAM-ROM Interface/ROMD5: Z20.14 (OUT); also elsewhere on the board
/RAM-ROM Interface/ROMD6: Z14.14 (OUT); also elsewhere on the board
/RAM-ROM Interface/ROMD7: Z13.14 (OUT); also elsewhere on the board
GND: Z13.16 (VSS), Z14.16 (VSS), Z15.16 (VSS), Z16.16 (VSS), Z17.16 (VSS), Z18.16 (VSS), Z19.16 (VSS), Z20.16 (VSS), Z35.8 (GND), Z35.15 (E), Z51.8 (GND), Z51.15 (E), Z67.12, Z68.12, Z68.15, Z71.9, Z71.11; also elsewhere on the board
unnamed: R66.2, Z71.10
unnamed: Z13.5 (A0), Z14.5 (A0), Z15.5 (A0), Z16.5 (A0), Z17.5 (A0), Z18.5 (A0), Z19.5 (A0), Z20.5 (A0), Z35.4 (Za)
unnamed: Z13.7 (A1), Z14.7 (A1), Z15.7 (A1), Z16.7 (A1), Z17.7 (A1), Z18.7 (A1), Z19.7 (A1), Z20.7 (A1), Z35.7 (Zb)
unnamed: Z13.6 (A2), Z14.6 (A2), Z15.6 (A2), Z16.6 (A2), Z17.6 (A2), Z18.6 (A2), Z19.6 (A2), Z20.6 (A2), Z35.9 (Zc)
unnamed: Z13.12 (A3), Z14.12 (A3), Z15.12 (A3), Z16.12 (A3), Z17.12 (A3), Z18.12 (A3), Z19.12 (A3), Z20.12 (A3), Z35.12 (Zd)
unnamed: Z13.11 (A4), Z14.11 (A4), Z15.11 (A4), Z16.11 (A4), Z17.11 (A4), Z18.11 (A4), Z19.11 (A4), Z20.11 (A4), Z51.4 (Za)
unnamed: Z13.10 (A5), Z14.10 (A5), Z15.10 (A5), Z16.10 (A5), Z17.10 (A5), Z18.10 (A5), Z19.10 (A5), Z20.10 (A5), Z51.7 (Zb)
unnamed: Z13.13 (A6), Z14.13 (A6), Z15.13 (A6), Z16.13 (A6), Z17.13 (A6), Z18.13 (A6), Z19.13 (A6), Z20.13 (A6), Z71.13, Z71.14
unnamed: R57.2, Z13.15 (~CAS), Z14.15 (~CAS), Z15.15 (~CAS), Z16.15 (~CAS), Z17.15 (~CAS), Z18.15 (~CAS), Z19.15 (~CAS), Z20.15 (~CAS), Z67.13
unnamed: R60.2, Z13.4 (~RAS), Z14.4 (~RAS), Z15.4 (~RAS), Z16.4 (~RAS), Z17.4 (~RAS), Z18.4 (~RAS), Z19.4 (~RAS), Z20.4 (~RAS), Z68.13
unnamed: Z35.3 (I1a), Z71.1, Z71.2, Z71.7, Z71.8
unnamed: Z51.9 (Zc), Z71.3
unnamed: Z67.15, Z71.5, Z71.6

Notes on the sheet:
Memory Address Multiplexer
~{8k}
The RAM output stays in high-impedance without ~{CAS}
8/16k
Used to avoid Data-Out contention between ROM and RAM for 8/16k RAM configurations
~{CS} for 4k DRAM
Depending on 8k module used, A0 on ~{CAS} needs to be held Hi or Low
16k

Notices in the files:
README.md:
License:
This project is licensed under the MIT License - see the [LICENSE](LICENSE) file for details.
